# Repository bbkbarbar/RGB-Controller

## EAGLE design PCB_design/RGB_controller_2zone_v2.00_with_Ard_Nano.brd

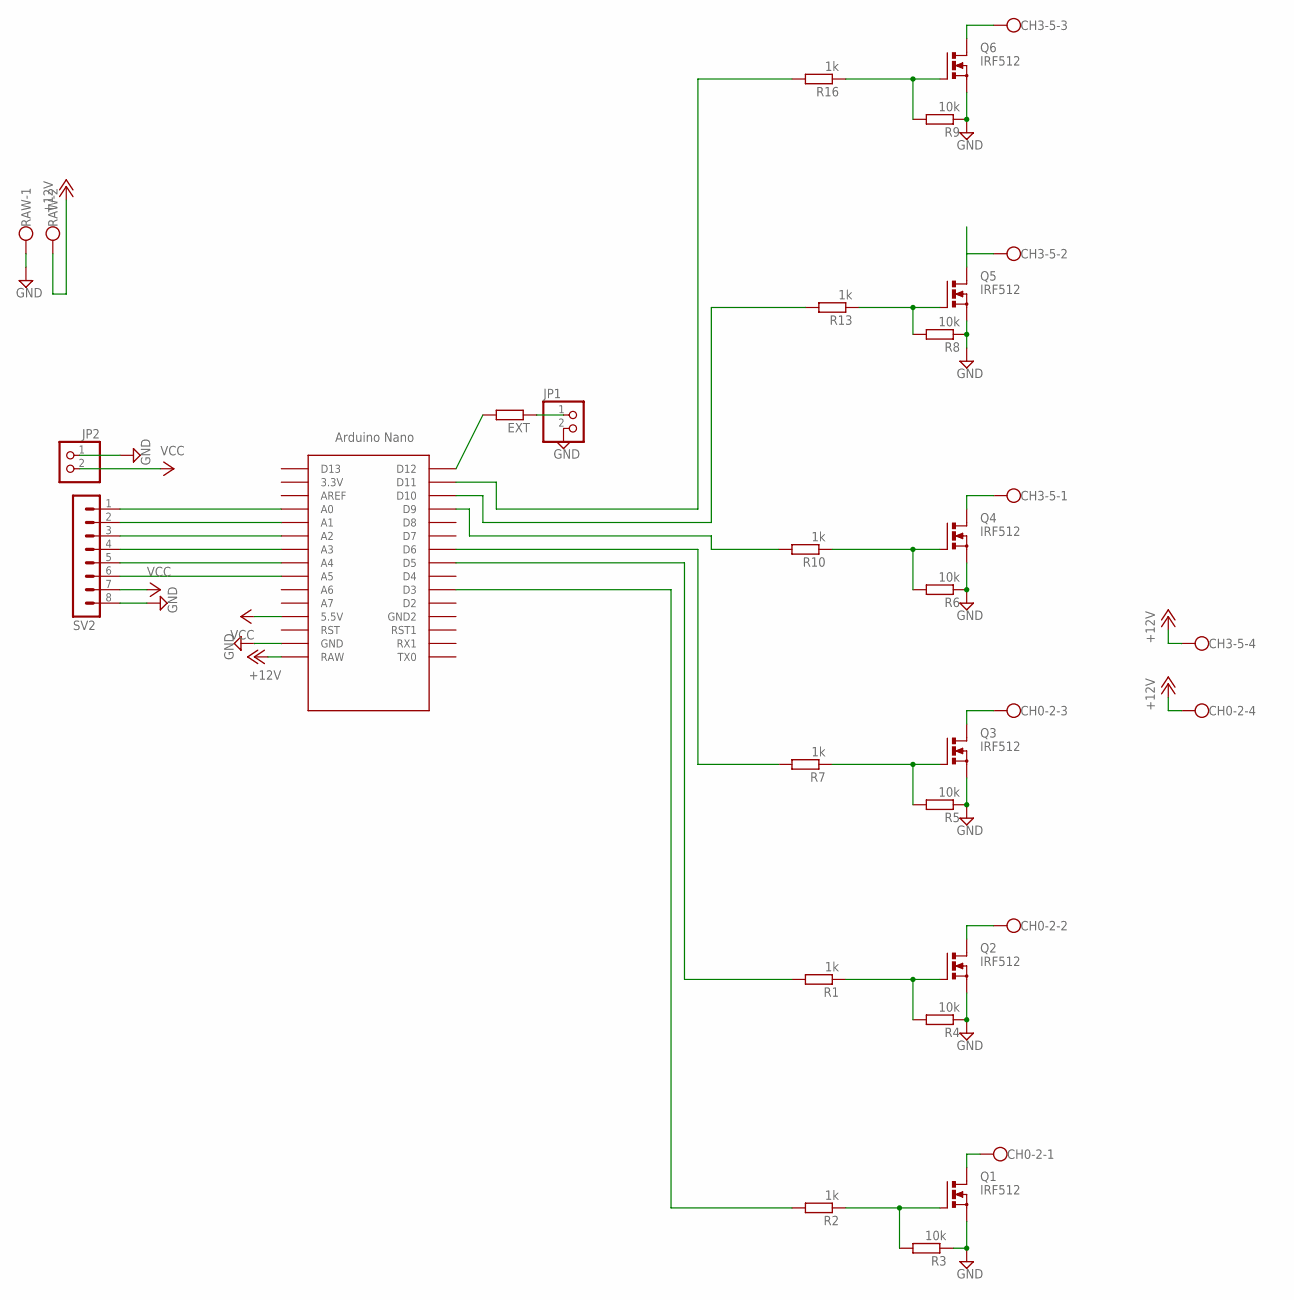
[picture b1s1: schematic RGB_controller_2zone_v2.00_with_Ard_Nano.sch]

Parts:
CH0-2, CH3-5: W237-4
EXT: R-EU_0207/10; 0207/10
JP1, JP2: PINHD-1X2; 1X02
Q1, Q2, Q3, Q4, Q5, Q6: IRF512; TO220BV
R1, R2, R7, R10, R13, R16: 1k; 0207/10
R3, R4, R5, R6, R8, R9: 10k; 0207/10
RAW: W237-102
SV2: MA08-1
U$1: NANO

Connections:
+12V: CH0-2.4, CH3-5.4, RAW.2, U$1.RAW
A0: SV2.1, U$1.A0
A1: SV2.2, U$1.A1
A2: SV2.3, U$1.A2
A3: SV2.4, U$1.A3
A4-D18: SV2.5, U$1.A4
A4-D19: SV2.6, U$1.A5
D12: EXT.2, U$1.D12
GATE_1: Q1.G, R2.1, R3.2
GATE_2: Q2.G, R1.1, R4.2
GATE_3: Q3.G, R5.2, R7.1
GATE_4: Q4.G, R6.2, R10.1
GATE_5: Q5.G, R8.2, R13.1
GATE_6: Q6.G, R9.2, R16.1
GND: JP1.2, JP2.1, Q1.S, Q2.S, Q3.S, Q4.S, Q5.S, Q6.S, R3.1, R4.1, R5.1, R6.1, R8.1, R9.1, RAW.1, SV2.8, U$1.GND
IC_PWM_OUT_0: R2.2, U$1.D3
IC_PWM_OUT_1: R1.2, U$1.D5
IC_PWM_OUT_2: R7.2, U$1.D6
IC_PWM_OUT_3: R10.2, U$1.D9
IC_PWM_OUT_4: R13.2, U$1.D10
IC_PWM_OUT_5: R16.2, U$1.D11
unnamed: EXT.1, JP1.1
OUTPUT_0: CH0-2.1, Q1.D
OUTPUT_1: CH0-2.2, Q2.D
OUTPUT_2: CH0-2.3, Q3.D
OUTPUT_3: CH3-5.1, Q4.D
OUTPUT_4: CH3-5.2, Q5.D
OUTPUT_5: CH3-5.3, Q6.D
VCC: JP2.2, SV2.7, U$1.5V (5.5V)

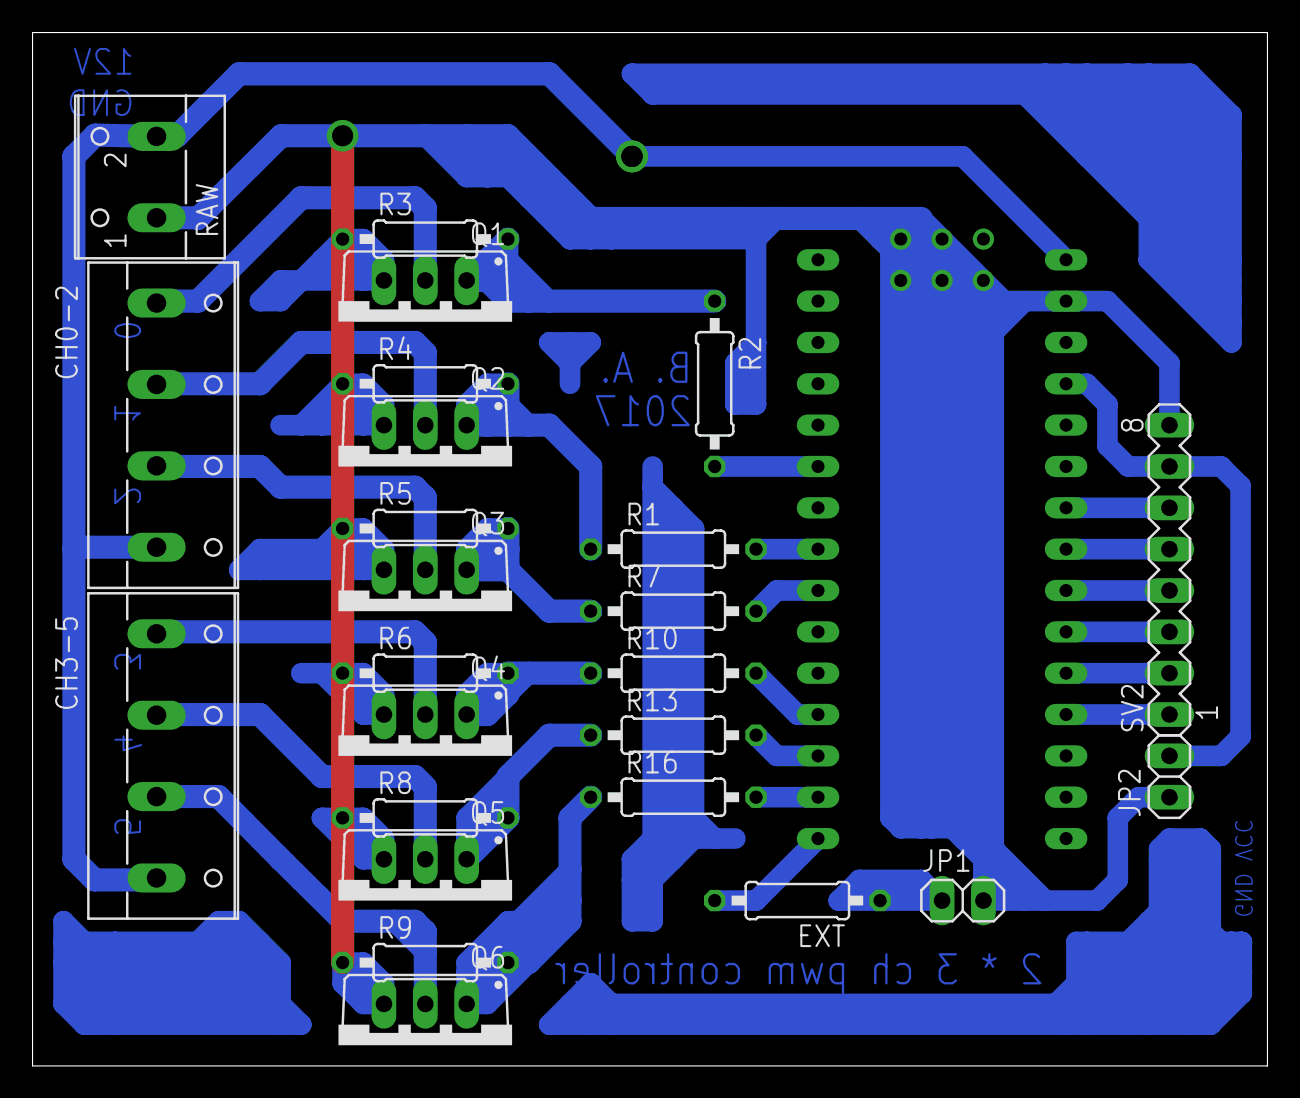
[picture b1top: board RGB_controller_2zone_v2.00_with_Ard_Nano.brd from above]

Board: 2 copper layers, 75.9 x 63.5 mm, 26 parts (0 on the bottom side), 29 nets.

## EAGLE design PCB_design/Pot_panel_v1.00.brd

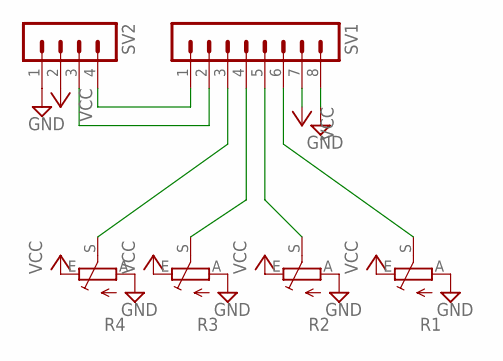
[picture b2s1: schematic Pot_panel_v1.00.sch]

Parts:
R1, R2, R3, R4: TRIM_EU-CA6V; CA6V
SV1: MA08-1
SV2: MA04-1

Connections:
A0: R1.S, SV1.6
A1: R2.S, SV1.5
A2: R3.S, SV1.4
A3: R4.S, SV1.3
GND: R1.A, R2.A, R3.A, R4.A, SV1.8, SV2.1
unnamed: SV1.1, SV2.4
unnamed: SV1.2, SV2.3
VCC: R1.E, R2.E, R3.E, R4.E, SV1.7, SV2.2

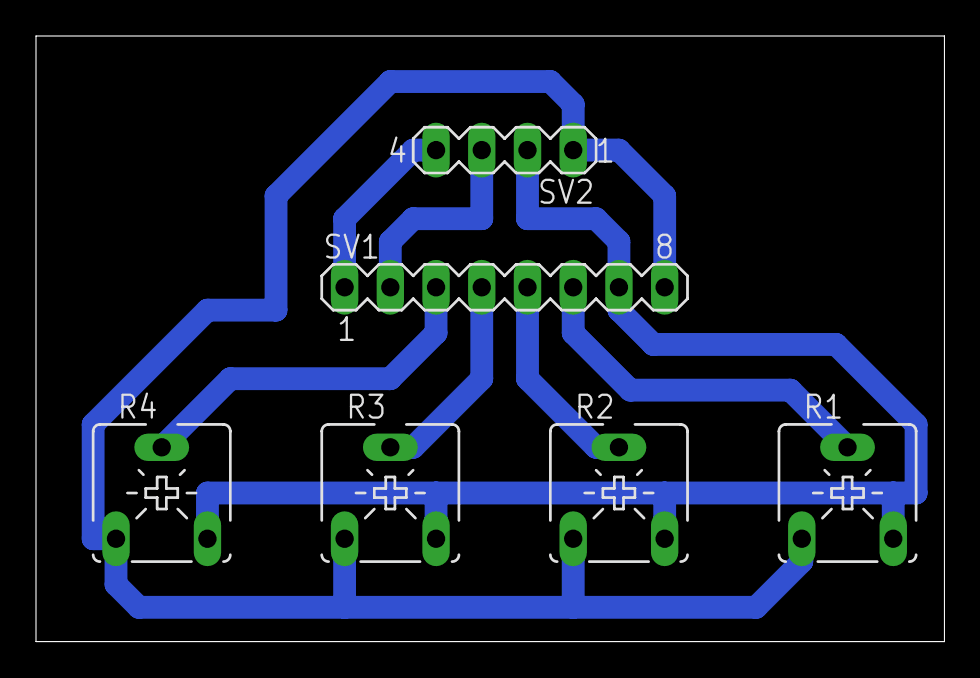
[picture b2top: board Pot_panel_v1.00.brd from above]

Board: 2 copper layers, 50.5 x 33.6 mm, 6 parts (0 on the bottom side), 8 nets.

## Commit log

2017-04-04 Add readme, init repo
2017-04-04 Add gitIgnore
2017-04-04 Add schematics and board design
2017-04-04 Add printable board design PDFs
2017-04-04 Add firmware skeletonű
2017-04-04 Add HeStore basket only for boards
2017-04-04 Add HeStore basket only for boards and addtitional materials
2017-04-04 Skeleton for testing on breadboard
2017-04-04 Create partlists
2017-04-05 Add demo code for 2-sided pulse
2017-04-05 Change arduino layout to fit to the buyable clone
2017-04-07 Add PCB design with Arduino Nano
2017-04-09 Update PCB for using arduino nano
2017-04-13 Update code with using potmeters
2017-04-13 Show setted color on start for 1-1 sec
2017-04-13 Add handling of 2 further potmeters to set boundary values of shining
2017-04-13 Useage of potmeters for boundary values of shining is optional with defining POT_MIN and POT_MAX macros
2017-04-15 RC verison (v1.02)
